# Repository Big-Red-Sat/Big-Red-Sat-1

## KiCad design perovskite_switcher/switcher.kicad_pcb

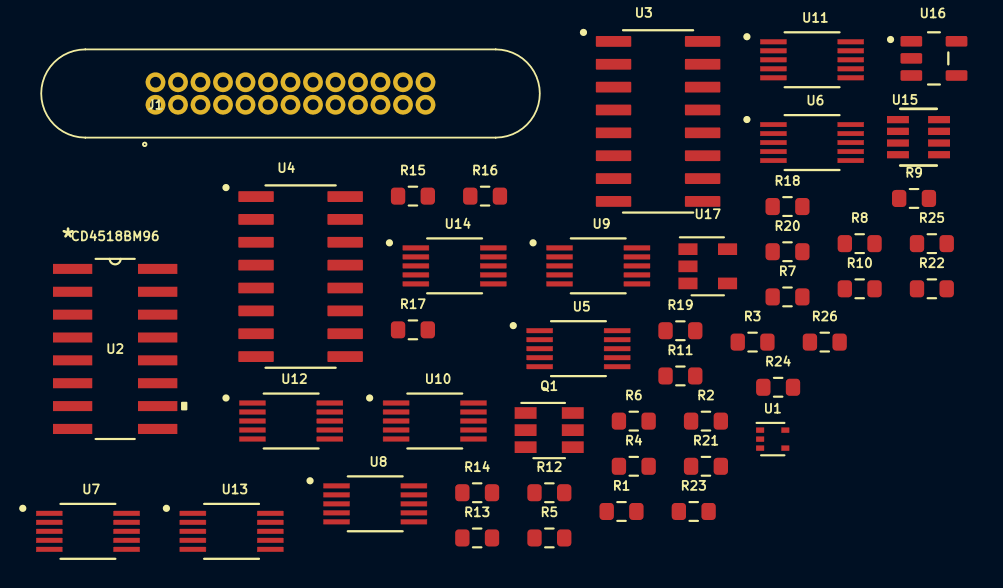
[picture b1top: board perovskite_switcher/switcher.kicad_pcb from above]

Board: 2 copper layers, 45 parts (0 on the bottom side), 81 nets, no tracks yet.

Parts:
J1: G125-MV12605M1P
Q1: DMC2053UVT; TSOT-23-6
R1: 1k; R_0603_1608Metric
R2, R3: 10k; R_0603_1608Metric
R4, R5, R6, R7, R8, R9, R10, R11, R12, R13, R14, R15, R16, R17, R18, R19, R20, R21, R22, R23, R25: R; R_0603_1608Metric
R24: 20k; R_0603_1608Metric
R26: 1; R_0603_1608Metric
U1: SN74LVC1G14DRL; SOT-553
U2: CD4518BM96
U3, U4: CD4028BMT; SOIC127P600X175-16N
U5, U6, U7, U8, U9, U10, U11, U12, U13, U14: MAX4736EUBT; SOP50P490X110-10N
U15: LT3092ETS8TRPBF; TSOT-23_TS8
U16: INA180B2IDBVT; SOT95P280X145-5N
U17: MCP6401RT-xOT; SOT-23-5

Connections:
+3V3: Q1.2, R3.1, U1.5, U2.16, U3.16, U4.16, U5.8, U6.8, U7.8, U8.8, U9.8, U10.8, U11.8, U12.8, U13.8, U14.8, U16.5, U17.2
/Perovskite Switches/ENABLE_PANEL_SWITCH: U1.2, U2.10
/Perovskite Switches/RESET_PANEL_SWITCH: U2.7, U2.15
/Perovskite Switches/V_PANEL: R25.1, U16.3, U17.3
/Perovskite Switches/V_PANEL_MEASURE: U17.1, U17.4
GND: Q1.5, R2.2, R4.1, R5.1, R6.1, R7.1, R8.1, R9.1, R10.1, R11.1, R12.1, R13.1, R14.1, R15.1, R16.1, R17.1, R18.1, R19.1, R20.1, R21.1, R22.1, R23.1, U1.3, U2.8, U3.8, U4.8, U5.3, U6.3, U7.3, U8.3, U9.3, U10.3, U11.3, U12.3, U13.3, U14.3, U16.2, U17.5
unnamed: J1.1, U5.10
unnamed: J1.2, U5.6
unnamed: J1.3, U6.10
unnamed: J1.4, U6.6
unnamed: J1.5, U7.10
unnamed: J1.6, U7.6
unnamed: J1.7, U8.10
unnamed: J1.8, U8.6
unnamed: J1.9, U9.10
unnamed: J1.10, U9.6
unnamed: J1.11, U10.10
unnamed: J1.12, U10.6
unnamed: J1.13, U11.10
unnamed: J1.14, U14.10
unnamed: J1.15, U13.6
unnamed: J1.16, U13.10
unnamed: J1.17, U12.6
unnamed: J1.18, U12.10
unnamed: J1.19, U11.6
unnamed: Q1.1, R1.1, R2.1
unnamed: Q1.3, Q1.6, R3.2
unnamed: Q1.4, U15.7, U15.8
unnamed: R4.2, U5.9
unnamed: R5.2, U5.7
unnamed: R6.2, U6.9
unnamed: R7.2, U6.7
unnamed: R8.2, U7.9
unnamed: R9.2, U7.7
unnamed: R10.2, U8.9
unnamed: R11.2, U8.7
unnamed: R12.2, U9.9
unnamed: R13.2, U9.7
unnamed: R14.2, U10.9
unnamed: R15.2, U10.7
unnamed: R16.2, U11.9
unnamed: R17.2, U11.7
unnamed: R18.2, U12.9
unnamed: R19.2, U12.7
unnamed: R20.2, U13.9
unnamed: R21.2, U13.7
unnamed: R22.2, U14.9
unnamed: R23.2, U14.7
unnamed: R24.1, R26.1, U14.6
unnamed: R24.2, U15.5
unnamed: R25.2, U5.2, U5.4, U6.2, U6.4, U7.2, U7.4, U8.2, U8.4, U9.2, U9.4, U10.2, U10.4, U11.2, U11.4, U12.2, U12.4, U13.2, U13.4, U14.2, U14.4, U16.1
unnamed: R26.2, U15.2, U15.3, U15.4
unnamed: U1.4, U2.2
unnamed: U2.3, U3.10
unnamed: U2.4, U3.13
unnamed: U2.5, U3.12
unnamed: U2.6, U3.11
unnamed: U2.11, U4.10
unnamed: U2.12, U4.13
unnamed: U2.13, U4.12
unnamed: U2.14, U4.11
unnamed: U3.1, U7.5
unnamed: U3.2, U6.5
unnamed: U3.3, U5.5
unnamed: U3.4, U8.1
unnamed: U3.5, U9.1
unnamed: U3.6, U7.1
unnamed: U3.7, U8.5
unnamed: U3.9, U9.5
unnamed: U3.14, U5.1
unnamed: U3.15, U6.1
unnamed: U4.14, U10.1
unnamed: U4.3, U10.5
unnamed: U4.15, U11.1
unnamed: U4.2, U11.5
unnamed: U4.6, U12.1
unnamed: U4.1, U12.5
unnamed: U4.4, U13.1
unnamed: U4.7, U13.5
unnamed: U4.5, U14.1
unnamed: U4.9, U14.5

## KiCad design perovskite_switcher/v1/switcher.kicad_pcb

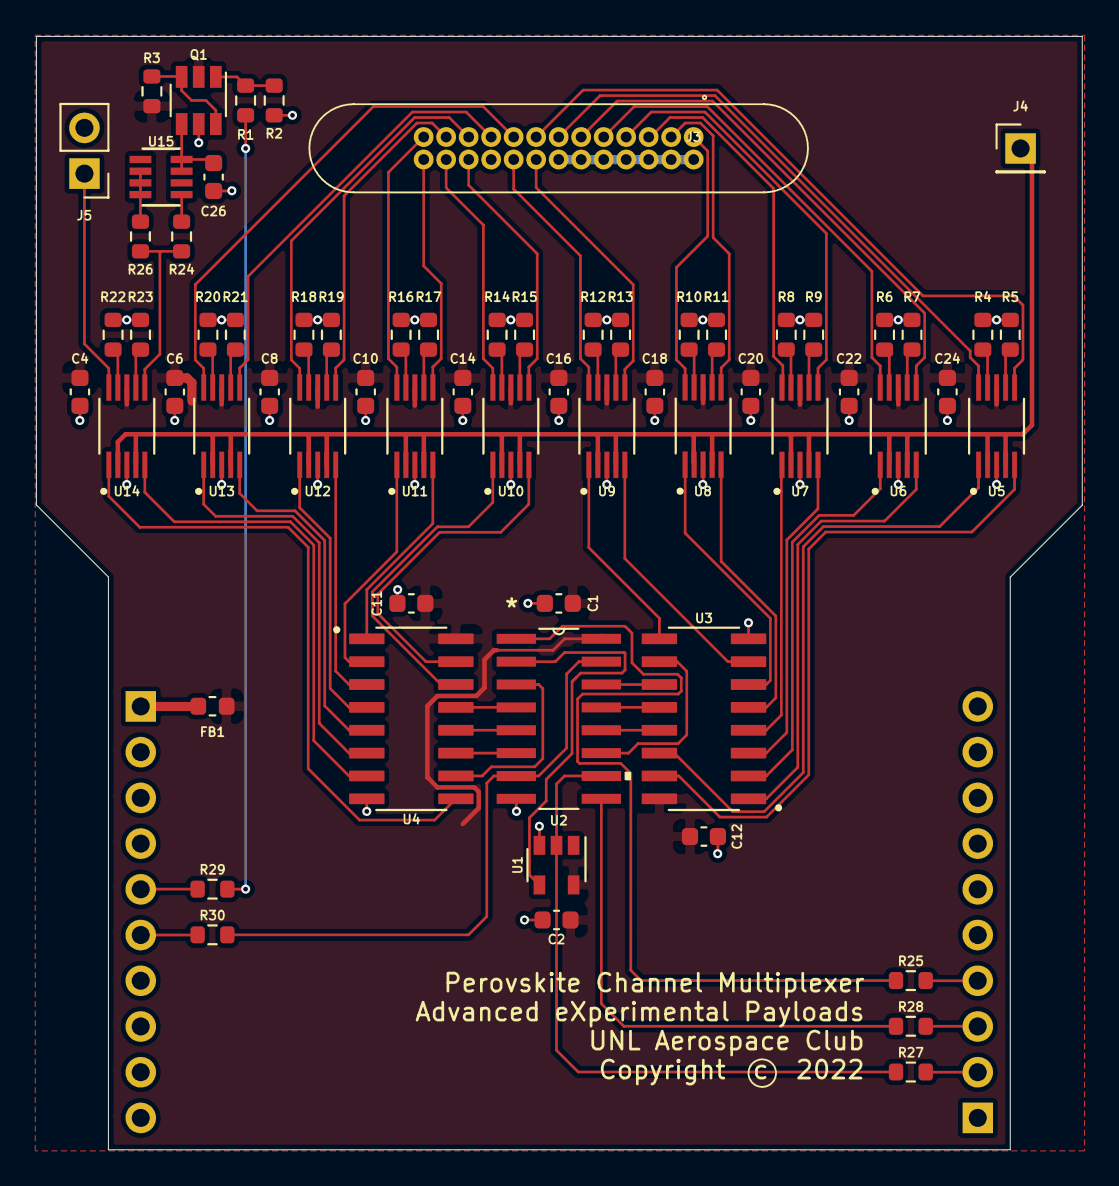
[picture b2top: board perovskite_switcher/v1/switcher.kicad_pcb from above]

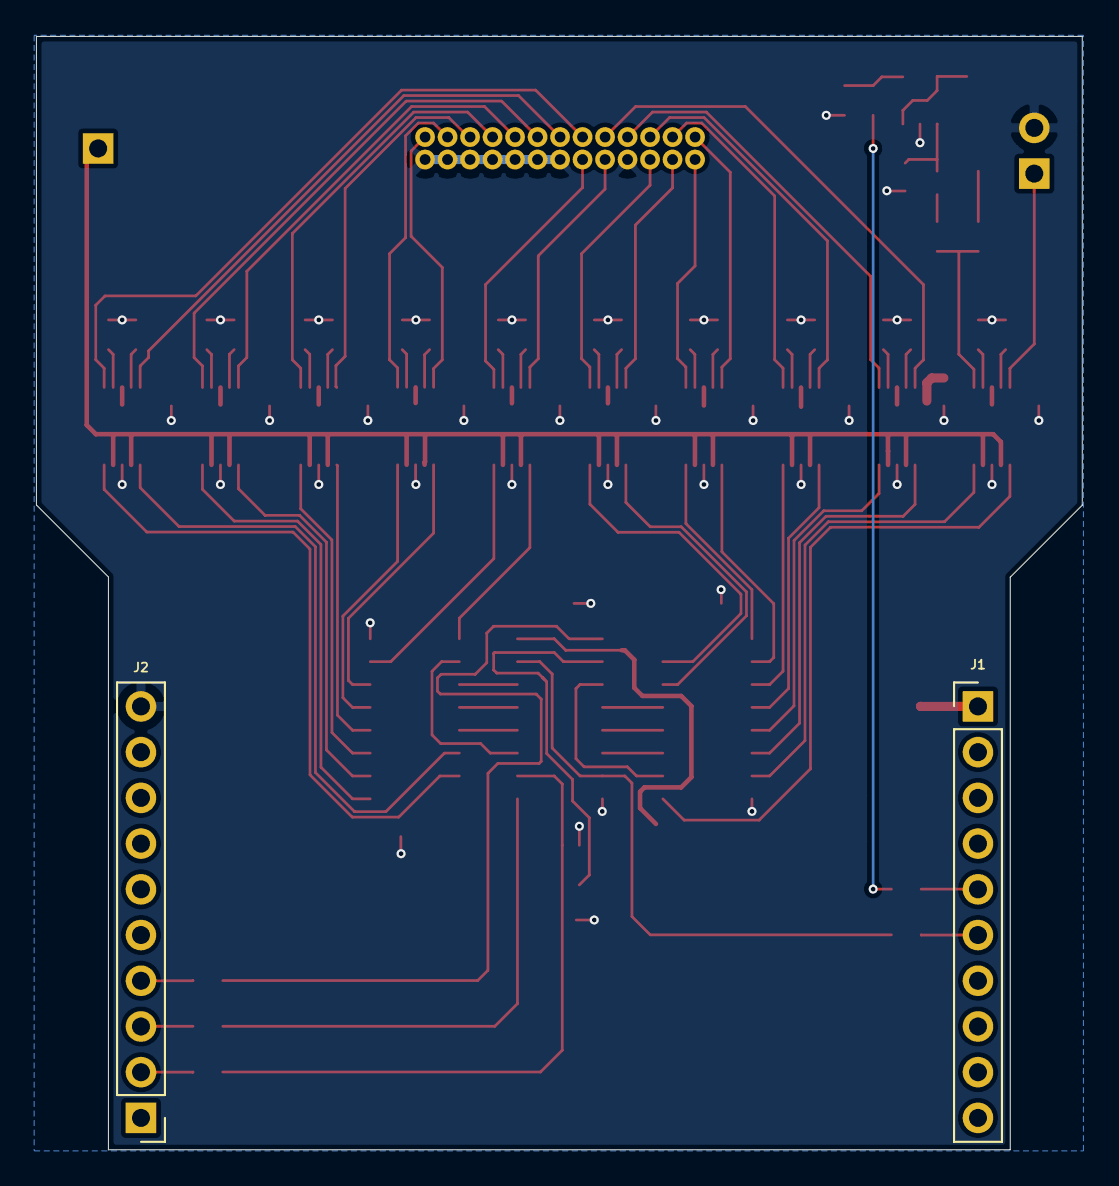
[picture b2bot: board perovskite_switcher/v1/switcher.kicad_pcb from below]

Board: 2 copper layers, 58.1 x 61.8 mm, 67 parts (2 on the bottom side), 88 nets.

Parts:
C1, C2, C4, C6, C8, C10, C11, C12, C14, C16, C18, C20, C22, C24, C26: 0.1u; C_0603_1608Metric
FB1: Ferrite_Bead; L_0603_1608Metric
J1, J2: Conn_01x10_Female; PinHeader_1x10_P2.54mm_Vertical
J3: G125-MV12605M1P
J4: Panel Output to Curve Tracer; PinHeader_1x01_P2.54mm_Vertical
J5: Silicon Cell; PinHeader_1x02_P2.54mm_Vertical
Q1: DMC2053UVT; TSOT-23-6
R1: 1k; R_0603_1608Metric
R2, R3: 10k; R_0603_1608Metric
R4, R5, R6, R7, R8, R9, R10, R11, R12, R13, R14, R15, R16, R17, R18, R19, R20, R21, R22, R23: R; R_0603_1608Metric
R24: 20k; R_0603_1608Metric
R25, R27, R28, R29, R30: 100; R_0603_1608Metric
R26: 1; R_0603_1608Metric
U1: SN74LVC1G14DRL; SOT-23-5
U2: CD4518BM96
U3, U4: CD4028BMT; SOIC127P600X175-16N
U5, U6, U7, U8, U9, U10, U11, U12, U13, U14: MAX4736EUBT; SOP50P490X110-10N
U15: LT3092ETS8TRPBF; TSOT-23_TS8

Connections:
0-9_CLOCK: R25.1, U2.1
10-19_CLOCK: R28.1, U2.9
+3V3: C1.1, C2.1, C4.1, C6.1, C8.1, C10.1, C11.1, C12.1, C14.1, C16.1, C18.1, C20.1, C22.1, C24.1, FB1.1, Q1.2, R3.1, U1.5, U2.16, U3.16, U4.16, U5.8, U6.8, U7.8, U8.8, U9.8, U10.8, U11.8, U12.8, U13.8, U14.8
ENABLE_PANEL_SWITCH: R27.1, U1.2, U2.10
ENABLE_TEST_SOURCE: R1.2, R29.1
GND: C1.2, C2.2, C4.2, C6.2, C8.2, C10.2, C11.2, C12.2, C14.2, C16.2, C18.2, C20.2, C22.2, C24.2, C26.1, J2.10, J3.14, J3.15, J3.16, J3.17, J3.18, J3.19, J3.20, J3.23, J5.2, Q1.5, R2.2, R4.1, R5.1, R6.1, R7.1, R8.1, R9.1, R10.1, R11.1, R12.1, R13.1, R14.1, R15.1, R16.1, R17.1, R18.1, R19.1, R20.1, R21.1, R22.1, R23.1, U1.3, U2.8, U3.8, U4.8, U5.3, U6.3, U7.3, U8.3, U9.3, U10.3, U11.3, U12.3, U13.3, U14.3
unnamed: C26.2, Q1.4, U15.7, U15.8
unnamed: FB1.2, J1.1
unnamed: J1.5, R29.2
unnamed: J1.6, R30.1
unnamed: J2.2, R27.2
unnamed: J2.3, R28.2
unnamed: J2.4, R25.2
unnamed: J3.1, U8.10
unnamed: J3.2, U8.6
unnamed: J3.3, U7.10
unnamed: J3.4, U7.6
unnamed: J3.5, U6.10
unnamed: J3.6, U6.6
unnamed: J3.7, U5.10
unnamed: J3.8, U5.6
unnamed: J3.9, U13.10
unnamed: J3.10, U13.6
unnamed: J3.11, U12.10
unnamed: J3.12, U12.6
unnamed: J3.13, U11.10
unnamed: J3.21, U9.6
unnamed: J3.22, U9.10
unnamed: J3.24, U10.6
unnamed: J3.25, U10.10
unnamed: J3.26, U11.6
unnamed: J4.1, U5.2, U5.4, U6.2, U6.4, U7.2, U7.4, U8.2, U8.4, U9.2, U9.4, U10.2, U10.4, U11.2, U11.4, U12.2, U12.4, U13.2, U13.4, U14.2, U14.4
unnamed: J5.1, U14.10
unnamed: Q1.1, R1.1, R2.1
unnamed: Q1.3, Q1.6, R3.2
unnamed: R4.2, U5.9
unnamed: R5.2, U5.7
unnamed: R6.2, U6.9
unnamed: R7.2, U6.7
unnamed: R8.2, U7.9
unnamed: R9.2, U7.7
unnamed: R10.2, U8.9
unnamed: R11.2, U8.7
unnamed: R12.2, U9.9
unnamed: R13.2, U9.7
unnamed: R14.2, U10.9
unnamed: R15.2, U10.7
unnamed: R16.2, U11.9
unnamed: R17.2, U11.7
unnamed: R18.2, U12.9
unnamed: R19.2, U12.7
unnamed: R20.2, U13.9
unnamed: R21.2, U13.7
unnamed: R22.2, U14.9
unnamed: R23.2, U14.7
unnamed: R24.1, R26.1, U14.6
unnamed: R24.2, U15.5
unnamed: R26.2, U15.2, U15.3, U15.4
unnamed: U1.4, U2.2
unnamed: U2.3, U4.10
unnamed: U2.4, U4.13
unnamed: U2.5, U4.12
unnamed: U2.6, U4.11
unnamed: U2.11, U3.10
unnamed: U2.12, U3.13
unnamed: U2.13, U3.12
unnamed: U2.14, U3.11
unnamed: U3.1, U6.5
unnamed: U3.2, U6.1
unnamed: U3.3, U7.5
unnamed: U3.4, U7.1
unnamed: U3.5, U8.5
unnamed: U3.6, U8.1
unnamed: U3.7, U9.5
unnamed: U3.9, U9.1
unnamed: U3.14, U5.1
unnamed: U3.15, U5.5
unnamed: U4.14, U10.1
unnamed: U4.15, U10.5
unnamed: U4.2, U11.1
unnamed: U4.1, U11.5
unnamed: U4.4, U12.1
unnamed: U4.3, U12.5
unnamed: U4.6, U13.1
unnamed: U4.5, U13.5
unnamed: U4.9, U14.1
unnamed: U4.7, U14.5
RESET_PANEL_SWITCH: R30.2, U2.7, U2.15

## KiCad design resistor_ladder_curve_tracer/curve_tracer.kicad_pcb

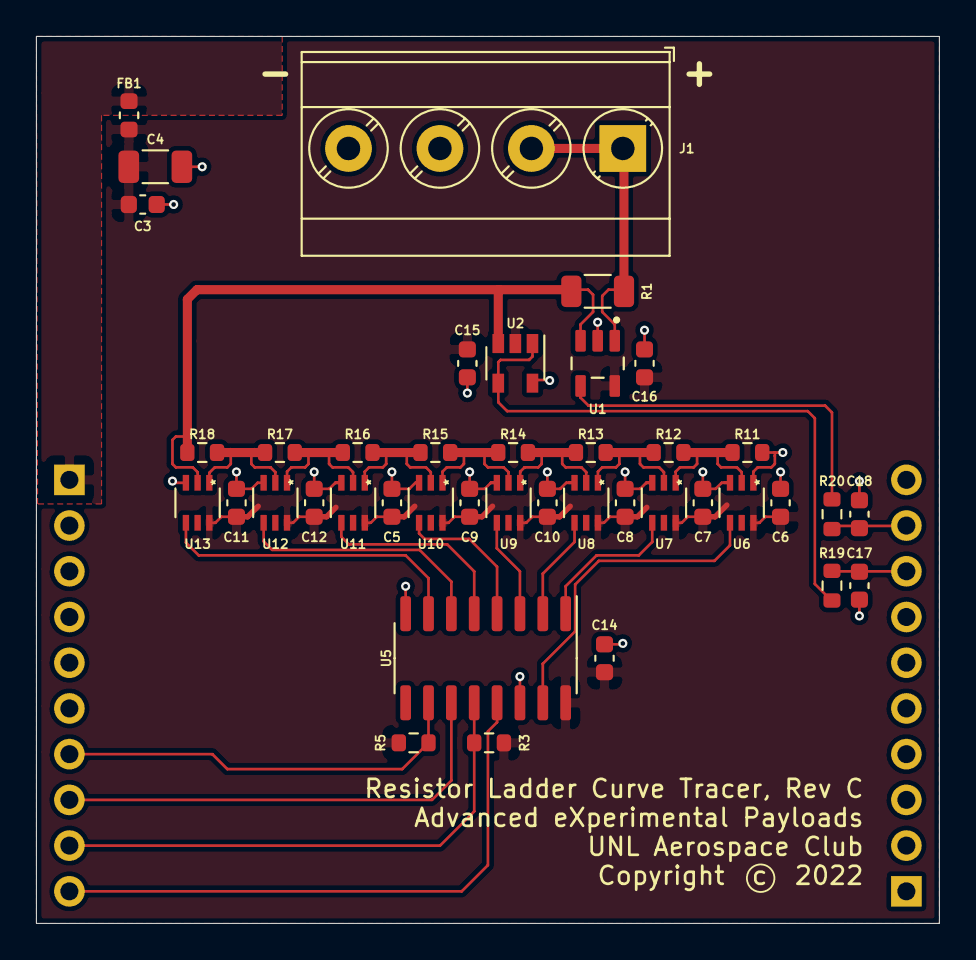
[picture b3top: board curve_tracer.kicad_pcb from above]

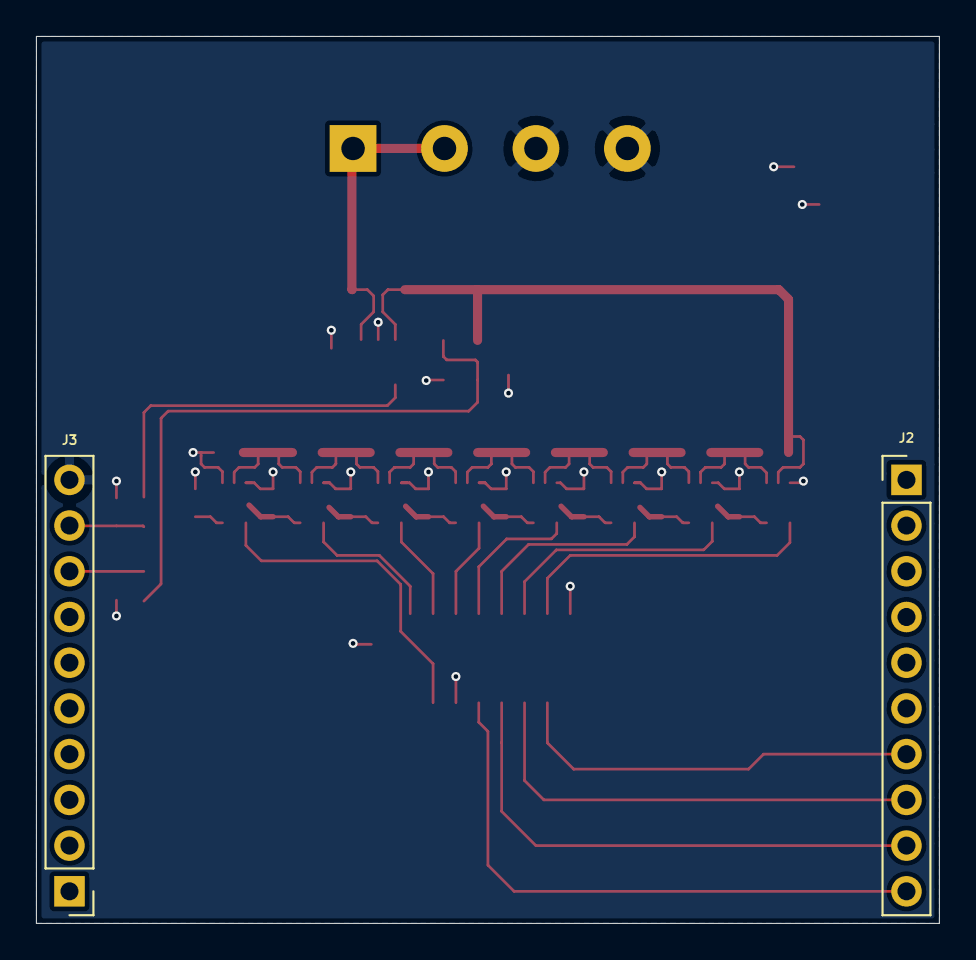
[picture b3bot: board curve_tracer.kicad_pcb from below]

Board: 2 copper layers, 50.2 x 49.3 mm, 43 parts (2 on the bottom side), 28 nets.

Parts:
C3: 1u; C_0603_1608Metric
C4: 10u; C_1206_3216Metric
C5, C6, C7, C8, C9, C10, C11, C12, C14, C15, C16: 0.1u; C_0603_1608Metric
C17, C18: 10u; C_0603_1608Metric
FB1: Ferrite_Bead; L_0603_1608Metric
J1: Screw_Terminal_01x04; TerminalBlock_Phoenix_MKDS-3-4-5.08_1x04_P5.08mm_Horizontal
J2, J3: Conn_01x10_Female; PinHeader_1x10_P2.54mm_Vertical
R1: R; R_1206_3216Metric
R3, R5, R19, R20: 10k; R_0603_1608Metric
R11: 50; R_0603_1608Metric
R12: 250; R_0603_1608Metric
R13: 500; R_0603_1608Metric
R14: 1000; R_0603_1608Metric
R15: 2000; R_0603_1608Metric
R16: 4000; R_0603_1608Metric
R17: 8000; R_0603_1608Metric
R18: 16000; R_0603_1608Metric
U1: INA180B2IDBVT; SOT95P280X145-5N
U2: MCP6401RT-xOT; SOT-23-5
U5: 74HC590; SOIC-16_3.9x9.9mm_P1.27mm
U6, U7, U8, U9, U10, U11, U12, U13: ADG841YKSZ-500RL7

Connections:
+3V3: C3.1, C4.1, C5.1, C6.1, C7.1, C8.1, C9.1, C10.1, C11.1, C12.1, C14.1, C15.1, C16.1, FB1.2, R3.2, R5.2, U1.5, U2.2, U5.16, U6.6, U7.6, U8.6, U9.6, U10.6, U11.6, U12.6, U13.6
/Panel Measurements/V_PANEL: R1.1, R18.1, U1.3, U2.3, U13.2
GND: C3.2, C4.2, C5.2, C6.2, C7.2, C8.2, C9.2, C10.2, C11.2, C12.2, C14.2, C15.2, C16.2, C17.2, C18.2, J1.3, J1.4, J3.10, R11.2, U1.2, U2.5, U5.8, U5.14, U6.1, U6.3, U7.3, U8.3, U9.3, U10.3, U11.3, U12.3, U13.3
I_PANEL_MEASURE: C18.1, J3.9, R20.2
LADDER_CLOCK: J2.8, U5.11
LADDER_EN: J2.9, R3.1, U5.12
LADDER_LATCH: J2.10, U5.13
LADDER_RESET: J2.7, R5.1, U5.10
unnamed: FB1.1, J2.1
unnamed: J1.1, J1.2, R1.2, U1.1
unnamed: R11.1, R12.2, U6.2, U7.1
unnamed: R12.1, R13.2, U7.2, U8.1
unnamed: R13.1, R14.2, U8.2, U9.1
unnamed: R14.1, R15.2, U9.2, U10.1
unnamed: R15.1, R16.2, U10.2, U11.1
unnamed: R16.1, R17.2, U11.2, U12.1
unnamed: R17.1, R18.2, U12.2, U13.1
unnamed: R19.1, U2.1, U2.4
unnamed: R20.1, U1.4
unnamed: U5.1, U7.4
unnamed: U5.2, U8.4
unnamed: U5.3, U9.4
unnamed: U5.15, U6.4
unnamed: U5.4, U10.4
unnamed: U5.5, U11.4
unnamed: U5.6, U12.4
unnamed: U5.7, U13.4
V_PANEL_MEASURE: C17.1, J3.8, R19.2

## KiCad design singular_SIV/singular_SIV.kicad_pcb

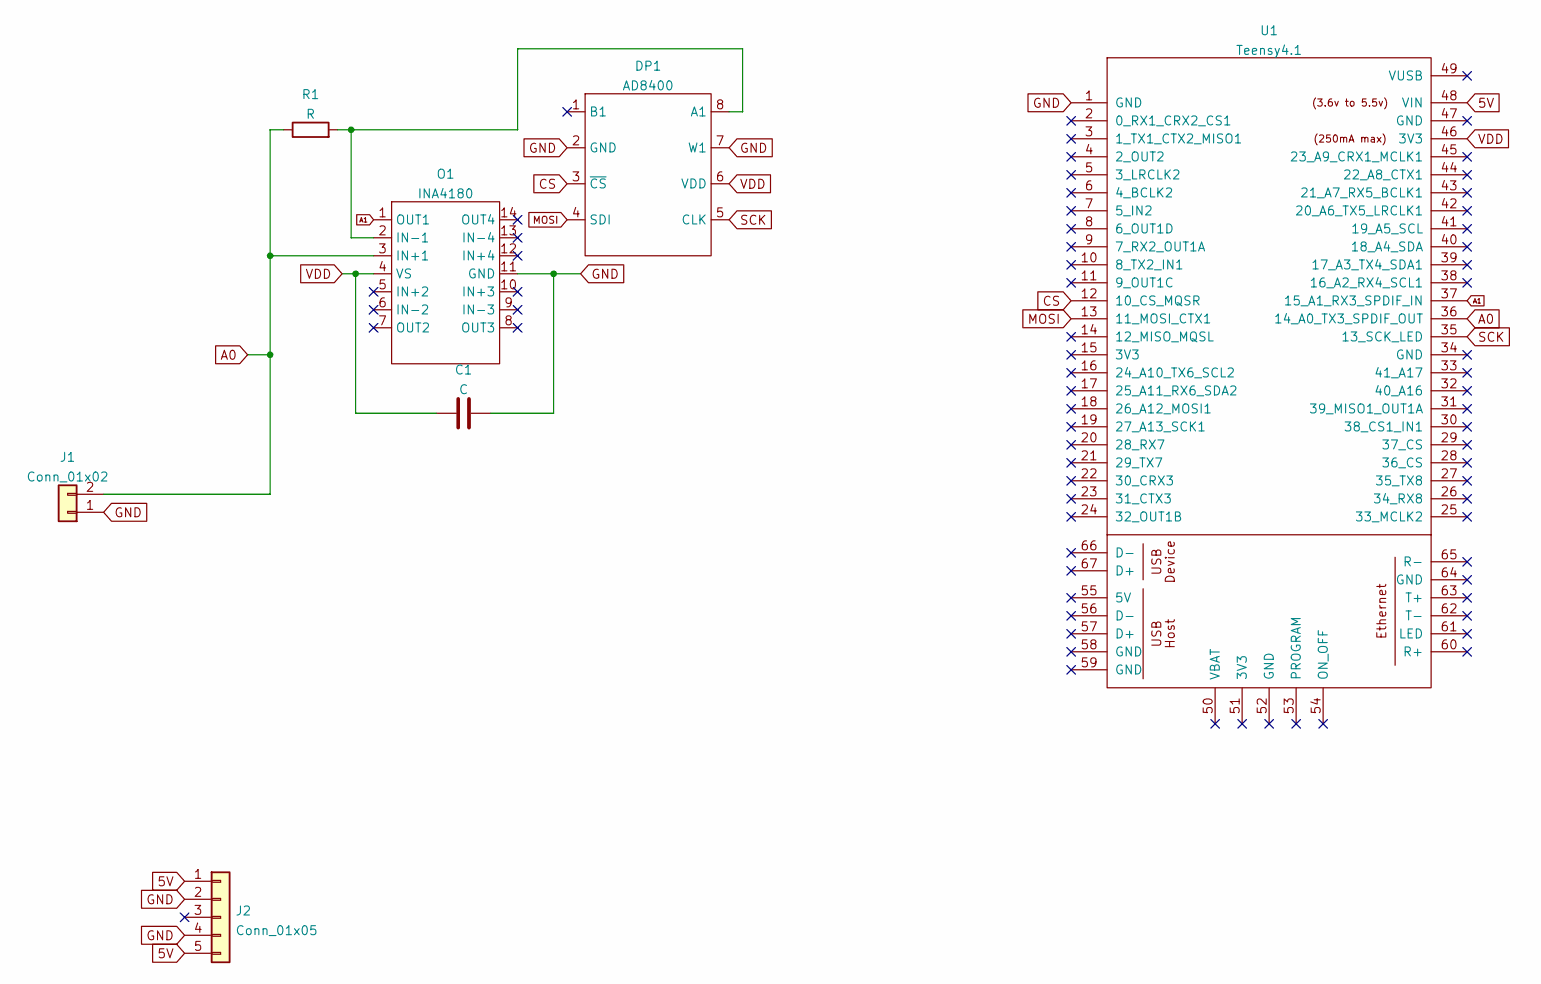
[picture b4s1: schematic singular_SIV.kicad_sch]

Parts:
C1: C; C_1206_3216Metric
DP1: AD8400; AD8400 DP
J1: Conn_01x02; PinHeader_1x02_P2.54mm_Vertical
J2: Conn_01x05; JST_XH_B5B-XH-A_1x05_P2.50mm_Vertical
O1: INA4180; SOP65P640X120-14N
R1: R; R_1206_3216Metric
U1: Teensy4.1; Teensy41

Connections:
5V: J2.1, J2.5, U1.48 (VIN)
A0: J1.2, O1.3 (IN+1), R1.1, U1.36 (14_A0_TX3_SPDIF_OUT)
A1: O1.1 (OUT1), U1.37 (15_A1_RX3_SPDIF_IN)
CS: DP1.3 (~CS), U1.12 (10_CS_MQSR)
GND: C1.2, DP1.2 (GND), DP1.7 (W1), J1.1, J2.2, J2.4, O1.11 (GND), U1.1 (GND)
MOSI: DP1.4 (SDI), U1.13 (11_MOSI_CTX1)
unnamed: DP1.8 (A1), O1.2 (IN-1), R1.2
SCK: DP1.5 (CLK), U1.35 (13_SCK_LED)
VDD: C1.1, DP1.6 (VDD), O1.4 (VS), U1.46 (3V3)

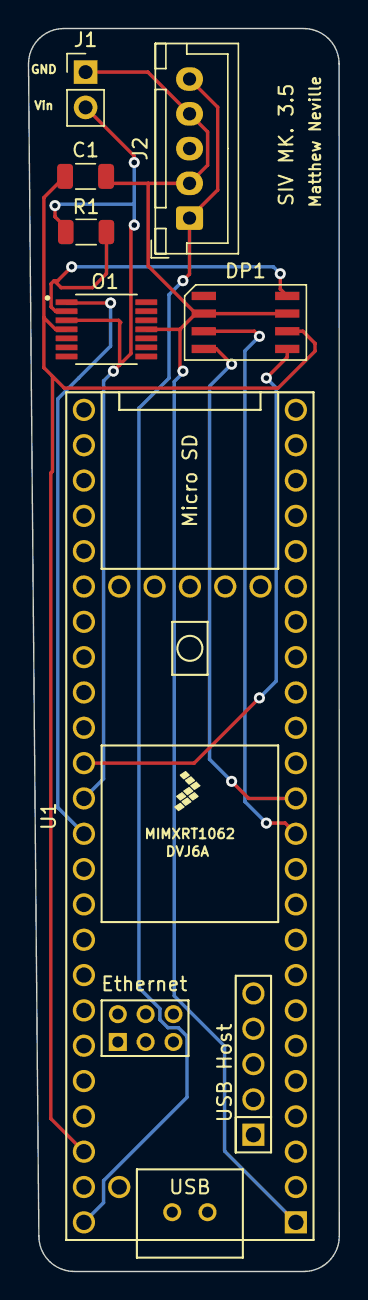
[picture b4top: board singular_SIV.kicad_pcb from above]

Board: 2 copper layers, 22.3 x 89.4 mm, 7 parts (0 on the bottom side), 9 nets.

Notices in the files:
perovskite_switcher/v1/switcher.kicad_pcb:
Copyright (c) 2022
parts and their libraries:
Copyright 2021 Accelerated Designs. All rights reserved.
